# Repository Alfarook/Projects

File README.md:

# Projects

College Projects/CAD Assignments

Alfarook Saleh

Robotics Project (part 1) video: https://www.youtube.com/watch?v=h9vVbkEvUp8&ab_channel=AlfarookSaleh

Description: Building and modeling a robotic arm via MATLAB by utilizing the MATLAB Robotics Toolkit, Appdesigner, and Object-Oriented programming. Showcasing an understanding of coordinate frames, transformation matrices, DH parameters, and model optimization. 

Robotics Project (part 2) video: https://www.youtube.com/watch?v=rTAVHGAOi9w&ab_channel=AlfarookSaleh

Description: Powering up the robotic arm from part 1 and implementing a control system. Developing methods and AI to control the arm and perform certain movements to play a game of tic-tac-toe against the robot either virtually or physically.

Digital Logic Design Final Project video: https://www.youtube.com/watch?v=A9aR_W_kF-A&ab_channel=AlfarookSaleh

Description: Using the software "Vivado" to connect and develop code for the Digilent Nexys4DDR board and create a digital safe. The safe has a pre-determined code to unlock it and the user is only allowed a maximum of 3 tries before it permanently locks. The only way to try again is to manually reset the board.

MATLAB Pendulum Project (part 1) video: https://www.youtube.com/watch?v=wV6XSgt2Cnw&ab_channel=AlfarookSaleh 

Description: Using MATLAB appdesigner to develop a GUI to activate an arduino and ultrasonic sensor. The GUI will record the ultrasonic sensor measuring the swing of a pendulum, display the recorded data, and use numerical methods to filter out incorrect data. The GUI can also save and load sets of data.

MATLAB Pendulum Project (part 2) video: https://www.youtube.com/watch?v=w-J1FyQOHM0&t=1s&ab_channel=AlfarookSaleh

Description: Further building upon the GUI from part 1, the GUI can now take and display the zeroes of the derivative of the data to find the swinging pendulum's period. A model of the pendulum can be derived from the length of the string used and the calculated period with matrix numerical methods such as Gauss Seidel and LU Decomposition. The gravitational constant can be approximated using the collected data and the theory of pendulums.

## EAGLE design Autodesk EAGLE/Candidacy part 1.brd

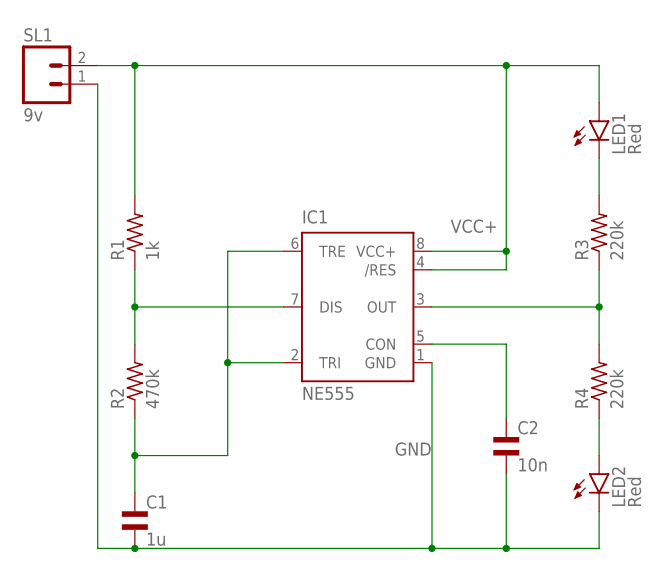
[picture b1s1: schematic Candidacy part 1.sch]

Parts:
C1: 1u; EU25-10
C2: 10n; EU25-10
IC1: NE555; DIL-08
LED1, LED2: Red; LED5MM
R1: 1k; 0204V
R2: 470k; 0204V
R3, R4: 220k; 0204V
SL1: 9v; 02P

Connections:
GND: C1.2, C2.2, IC1.1 (GND), LED2.K (C), SL1.1
unnamed: IC1.3 (OUT), R3.1, R4.2
unnamed: LED1.K (C), R3.2
unnamed: LED2.A, R4.1
unnamed: C1.1, IC1.2 (TRI), IC1.6 (TRE), R2.1
unnamed: IC1.7 (DIS), R1.1, R2.2
unnamed: C2.1, IC1.5 (CON)
VCC+: IC1.4 (/RES), IC1.8 (VCC+), LED1.A, R1.2, SL1.2

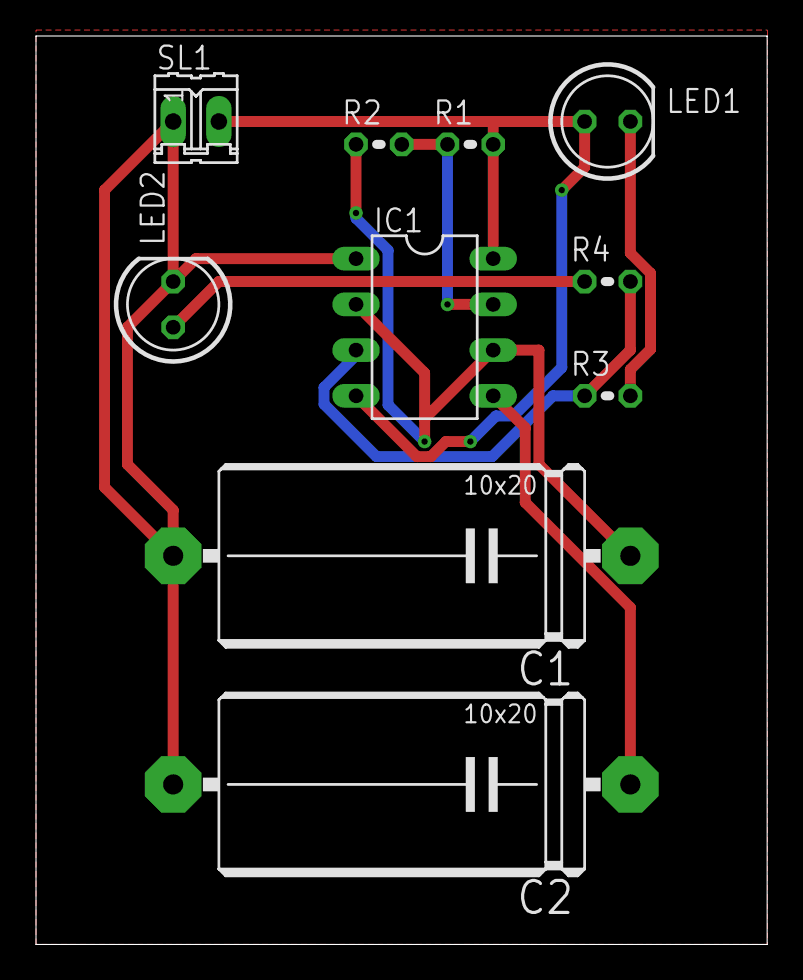
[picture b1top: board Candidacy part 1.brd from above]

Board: 2 copper layers, 40.6 x 50.5 mm, 10 parts (0 on the bottom side), 8 nets.

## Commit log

2021-10-15 Add files via upload
    CAD assignments from Wayne State
2021-10-15 Create Project 1 Video
2023-01-15 organizing files
2023-03-02 Updated NX 12.0 pics
    Updated NX 12.0 pics
2023-03-02 Digital Logic Design
2023-03-02 MATLAB
2023-03-02 CSC 2000
2023-03-02 Main Projects
